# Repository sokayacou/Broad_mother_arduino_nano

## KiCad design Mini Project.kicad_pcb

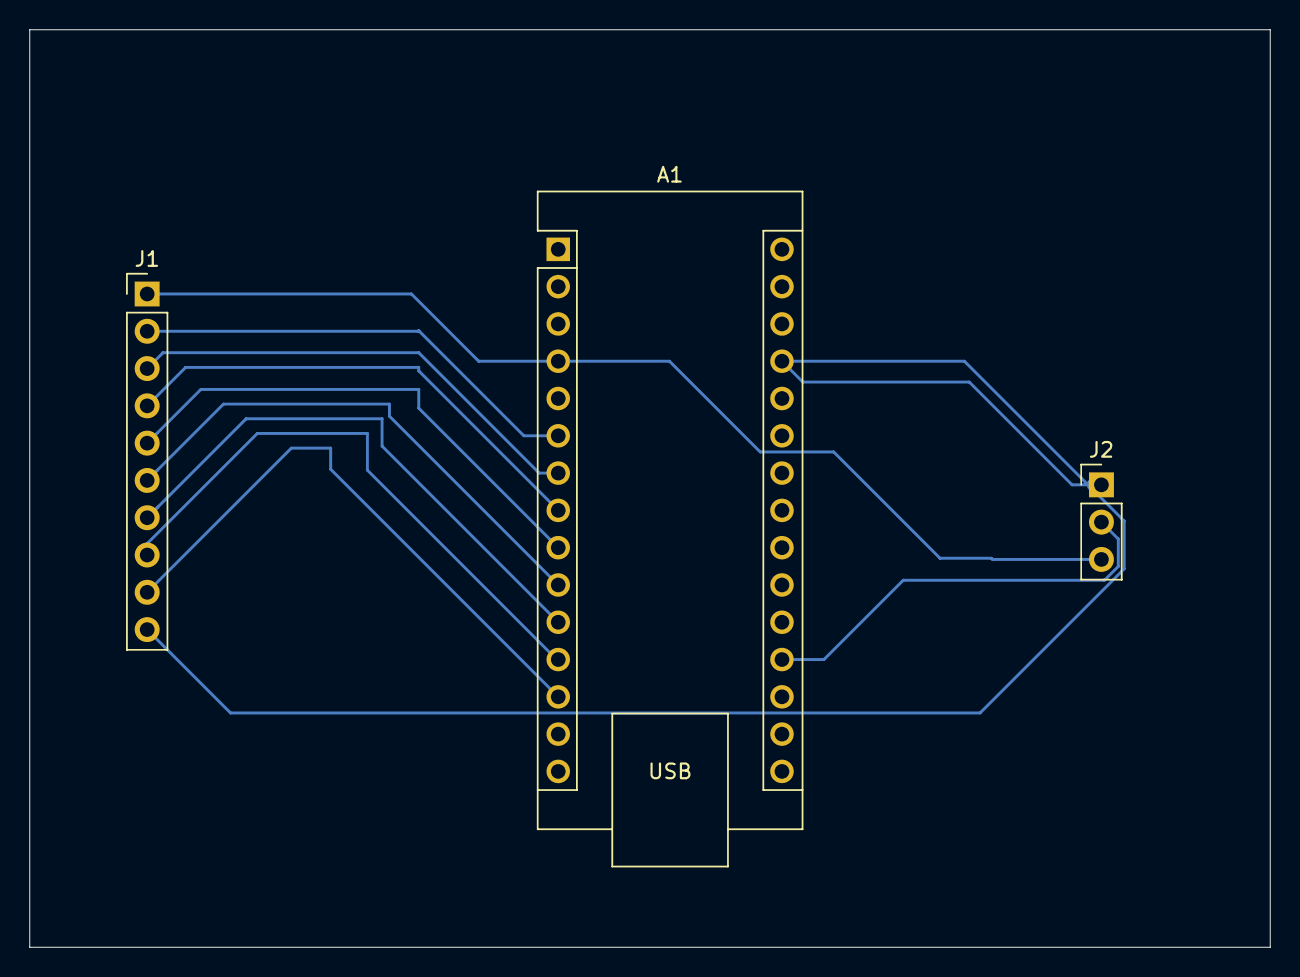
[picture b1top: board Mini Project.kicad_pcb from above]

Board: 2 copper layers, 84.5 x 62.5 mm, 3 parts (0 on the bottom side), 11 nets.

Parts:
A1: Arduino_Nano_v3.x; Arduino_Nano
J1: Conn_01x10; PinHeader_1x10_P2.54mm_Vertical
J2: Conn_01x03; PinHeader_1x03_P2.54mm_Vertical

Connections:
unnamed: A1.27 (+5V), J1.10, J2.1
unnamed: A1.19 (A0), J2.2
unnamed: A1.6 (D3), J1.2
unnamed: A1.7 (D4), J1.3
unnamed: A1.8 (D5), J1.4
unnamed: A1.9 (D6), J1.5
unnamed: A1.10 (D7), J1.6
unnamed: A1.11 (D8), J1.7
unnamed: A1.12 (D9), J1.8
unnamed: A1.13 (D10), J1.9
unnamed: A1.4 (GND), J1.1, J2.3
